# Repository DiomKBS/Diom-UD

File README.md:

# Unified Daughterboard Project

## Introduction
The Unified Daughterboard Project is an attempt by leading designers in the mechanical keyboard community to standardize the USB daughterboards used for their custom mechanical keyboard projects. It has initially been envisioned by users ai03, Wilba, Hineybush, Xelus, Xondat, aeryxz and Maximillian.

The main characteristic of this daughterboard is to integrate a USB Type C connector and the needed circuitry for USB2.0 operation in a small PCB that can be screwed to a keyboard chassis; this significantly simplifies the assembly and design of the main circuit board.

## C3 version

In its latest version, C3, this daughterboard features:

* ESD (Electrostatic Discharge) protection on the data lines of the USB connector through a specialized chip;
* Overcurrent protection through a PTC fuse;
* Overvoltage protection through a bidirectional TVS diode;
* Shielding noise decoupling capabilities through a ferrite bead;
* Single-path grounding of the metallic chassis to which the daughterboard is attached.
* Power Management and Voltage Protection

Adittionally, the C3 version is backwards compatible with both C1 and C2 versions since it has the same dimensions and uses the same screw hole sizes and positions, so keyboards designed using the past versions should also support C3.

## Detailed features

The figure below shows the schematic of the C3 version.

* U1 is the ESD protection for the USB data lines. It is a ultra-fast, low-capacitance chip specifically designed for USB type C connectors. When one of the data lines presents a sudden voltage spike, this chip promptly grounds it -- avoiding damage to the circuit that uses these lines;
* Resistors R1 and R2 are the CC resistors needed for operation of the USB Type C. These resistors are used by the USB host to know that the daughterboard is a downstream device and which side of the USBC connector is connected;
* Fuse F1 provides overcurrent protection. It is a PTC resettable;
* Diode D1 is a Transient Voltage Suppressor that exerpts to the power rails of the connector the same effect as the U1 chiup to data lines; when a voltge spike is detected, it shorts VCC and GND, aavoiding damage to the forward circuitry;
* Inductor L1 is a ferrite bead that presetns a very low impedance between the power ground and the signal ground in DC regimen; in high frequencies (for instance in an ESD event) it presents a very high impedance, avoiding noisy currents passing to the signal GND;
* The daughterboard features four screw holes used to fix it into a metal chassis. The top left mounting hole is shorted to the power ground signal; this means that the metal chassis of the keyboard will be grounded. However, the other three screw holes are not shorted to the power ground and are effectively isolated from that signal. This ensures that, in a discharge event emerging from the user providing charge to the system, the discharge current will have a single path through the daughterboard to the power ground; inductor L1 ensures that the discharge current is kept in the power ground plance and does not follow through to the signal ground.

## Designer/Consumer info and references
[View the wiki](https://github.com/ai03-2725/Unified-Daughterboard/wiki)

## Previews

## Credits
* [Gondolindrim](http://github.com/Gondolindrim)
* [ai03](http://github.com/ai03-2725)
* [Wilba](https://github.com/Wilba6582)
* [Hineybush](http://github.com/hineybush)
* [Xelus](http://github.com/Xelus22)
* Xondat
* [aeryxz](https://github.com/aeryxz)
* [Maximillian](https://github.com/Maximillian)
* [Upas](http://github.com/awkannan)

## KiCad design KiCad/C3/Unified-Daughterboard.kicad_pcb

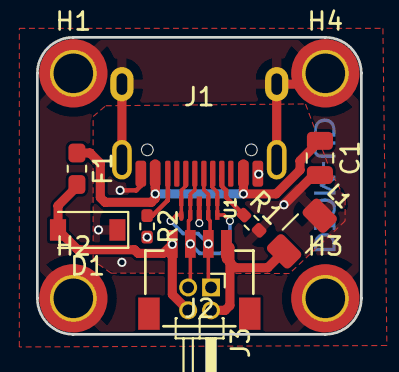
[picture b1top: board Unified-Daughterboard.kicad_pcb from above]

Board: 2 copper layers, 18.0 x 16.5 mm, 15 parts (1 on the bottom side), 9 nets.

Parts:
C1: 10u; C_0805_2012Metric
D1: SMF9.0CA; D_SOD-123
F1: ASMD1206-150; Fuse_0603_1608Metric_Pad1.05x0.95mm_HandSolder
G2: Unified-Daughterboard-Name; Unified-Daughterboard-Name.pretty
H1, H2, H3, H4: MountingHole_Pad; MountingHole_2.2mm_M2_DIN965_Pad_TopBottom
J1: TYPE-C-31-M12_13; TYPE-C-31-M-12
J2: SM04B-SRSS-TB(LF)(SN); JST-SR-4
J3: Conn_02x02_Odd_Even; PinHeader_2x02_P1.27mm_Horizontal
L1: 60R@100MHz; L_1206_3216Metric
R1, R2: 5.1k; R_0402_1005Metric_Pad0.72x0.64mm_HandSolder
U1: TPD4E05U06DQAR; USON-10_2.5x1.0mm_P0.5mm

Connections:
DA+: J1.A6 (D+), J1.B6 (D+), J2.3, J3.1, U1.1 (IO1), U1.4 (D2+), U1.7 (NC), U1.10 (NC)
DA-: J1.A7 (D-), J1.B7 (D-), J2.2, J3.3, U1.2 (IO2), U1.5 (D2-), U1.6 (NC), U1.9 (NC)
GND: J2.4, J3.2, L1.1
GNDPWR: H1.1, H2.1, H3.1, H4.1, J1.S (SHIELD)
GNDREF: C1.2, D1.1 (A1), J1.A1 (GND), J1.B1 (GND), L1.2, R1.2, R2.2, U1.3 (GND), U1.8 (GND)
unnamed: J1.A5 (CC1), R1.1
unnamed: J1.B5 (CC2), R2.1
VBUS: C1.1, F1.1, J1.A4 (VBUS), J1.B4 (VBUS)
VCC: D1.2 (A2), F1.2, J2.1, J3.4

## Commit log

2022-05-04 new design
2022-05-04 some changes
2022-05-04 logo
2022-05-12 change back and add decoupling cap
2022-06-19 minor changes
